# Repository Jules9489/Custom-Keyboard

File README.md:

# Custom-Keyboard

Plan:

65% Keyboard

Rotary Encoder for Media Controls 

Foam Padding in the Case 

Result:

A nice-looking 65% keyboard that has a rotary encoder for media controls.

It took me a while to make because I ran into different problems along the way, but I managed to fix them eventually. I learned a bit of RMK and a bit more about PCB design, as I had previously made a MacroPad using QMK but had a few flaws, and so I was able to learn from my previous mistakes to make this project better. I built this because I was going to buy a keyboard for my laptop, but then I saw this competition and decided to do it myself.

https://cad.onshape.com/documents/b6e58a4c59b5eab8ab909f70/w/83c04b1bc76860f5f25fe353/e/ed9d0ab061e5040caacf7854

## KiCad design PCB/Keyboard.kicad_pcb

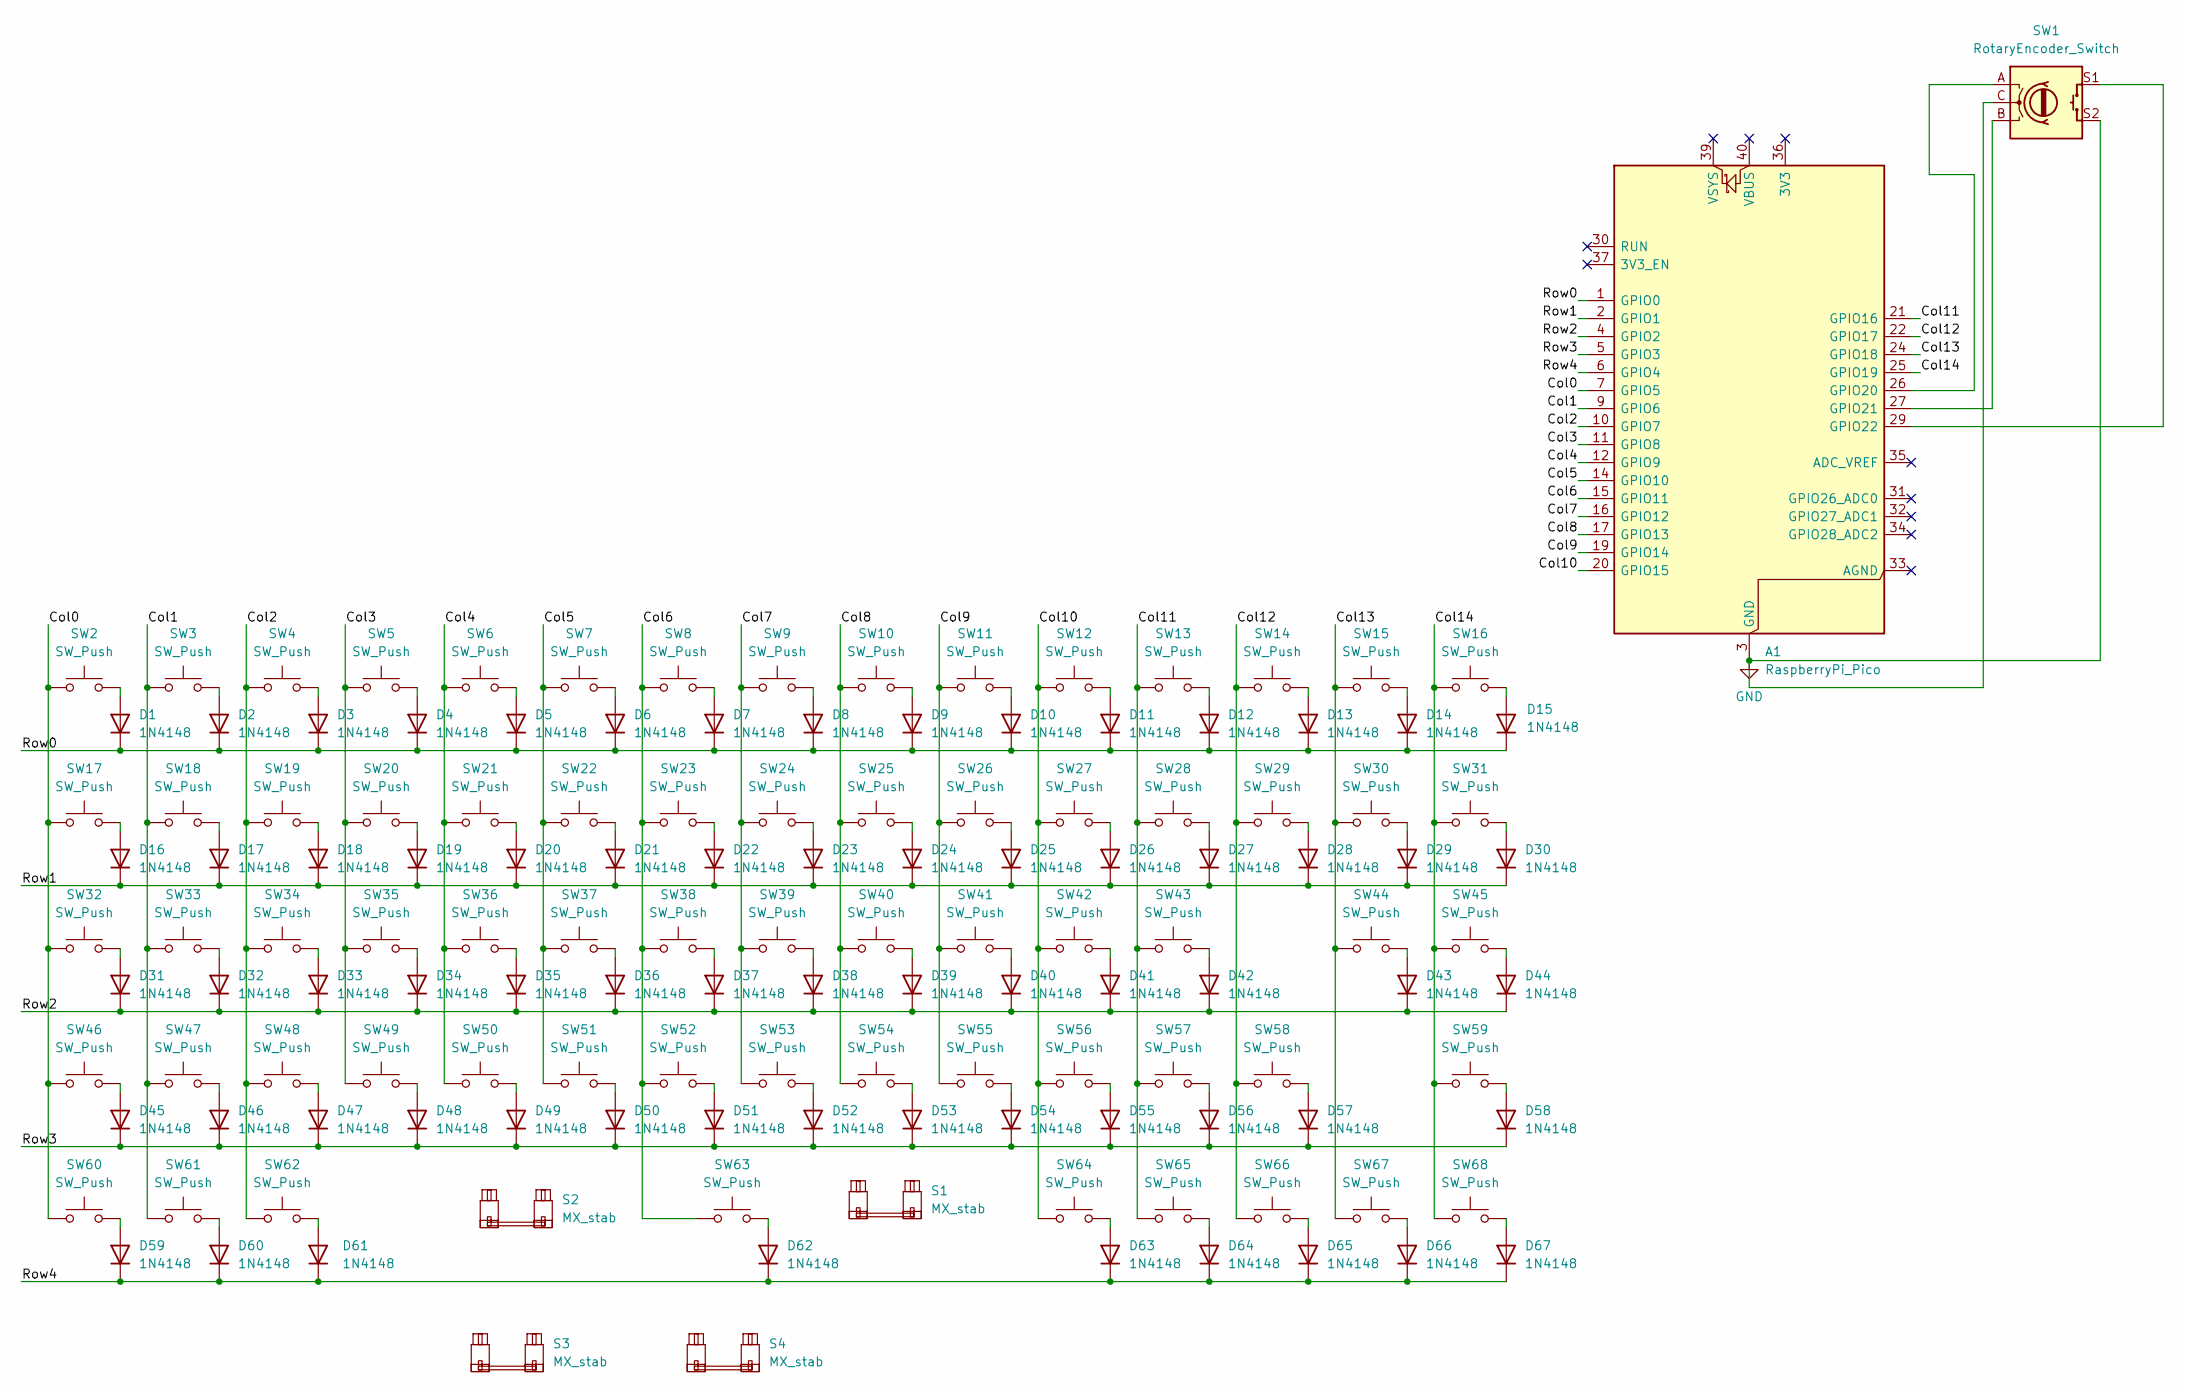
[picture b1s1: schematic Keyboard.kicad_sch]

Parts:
A1: RaspberryPi_Pico; RaspberryPi_Pico_Common_THT
D1, D2, D3, D4, D5, D6, D7, D8, D9, D10, D11, D12, D13, D14, D15, D16, D17, D18, D19, D20, D21, D22, D23, D24, D25, D26, D27, D28, D29, D30, D31, D32, D33, D34, D35, D36, D37, D38, D39, D40, D41, D42, D43, D44, D45, D46, D47, D48, D49, D50, D51, D52, D53, D54, D55, D56, D57, D58, D59, D60, D61, D62, D63, D64, D65, D66, D67: 1N4148; D_DO-35_SOD27_P7.62mm_Horizontal
S1: MX_stab; STAB_MX_P_6.25u
S2: MX_stab; STAB_MX_P_2.25u
S3, S4: MX_stab; STAB_MX_P_2u
SW1: RotaryEncoder_Switch; ROT_Alps_EC11E-Switch
SW2, SW3, SW4, SW5, SW6, SW7, SW8, SW9, SW10, SW11, SW12, SW13, SW14, SW15, SW16, SW17, SW18, SW19, SW20, SW21, SW22, SW23, SW24, SW25, SW26, SW27, SW28, SW29, SW30, SW31, SW32, SW33, SW34, SW35, SW36, SW37, SW38, SW39, SW40, SW41, SW42, SW43, SW44, SW45, SW46, SW47, SW48, SW49, SW50, SW51, SW52, SW53, SW54, SW55, SW56, SW57, SW58, SW59, SW60, SW61, SW62, SW63, SW64, SW65, SW66, SW67, SW68: SW_Push; SW_MX_1u

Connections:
/Col0: A1.7 (GPIO5), SW2.1, SW17.1, SW32.1, SW46.1, SW60.1
/Col1: A1.9 (GPIO6), SW3.1, SW18.1, SW33.1, SW47.1, SW61.1
/Col2: A1.10 (GPIO7), SW4.1, SW19.1, SW34.1, SW48.1, SW62.1
/Col3: A1.11 (GPIO8), SW5.1, SW20.1, SW35.1, SW49.1
/Col4: A1.12 (GPIO9), SW6.1, SW21.1, SW36.1, SW50.1
/Col5: A1.14 (GPIO10), SW7.1, SW22.1, SW37.1, SW51.1
/Col6: A1.15 (GPIO11), SW8.1, SW23.1, SW38.1, SW52.1, SW63.1
/Col7: A1.16 (GPIO12), SW9.1, SW24.1, SW39.1, SW53.1
/Col8: A1.17 (GPIO13), SW10.1, SW25.1, SW40.1, SW54.1
/Col9: A1.19 (GPIO14), SW11.1, SW26.1, SW41.1, SW55.1
/Col10: A1.20 (GPIO15), SW12.1, SW27.1, SW42.1, SW56.1, SW64.1
/Col11: A1.21 (GPIO16), SW13.1, SW28.1, SW43.1, SW57.1, SW65.1
/Col12: A1.22 (GPIO17), SW14.1, SW29.1, SW58.1, SW66.1
/Col13: A1.24 (GPIO18), SW15.1, SW30.1, SW44.1, SW67.1
/Col14: A1.25 (GPIO19), SW16.1, SW31.1, SW45.1, SW59.1, SW68.1
/Row0: A1.1 (GPIO0), D1.1 (K), D2.1 (K), D3.1 (K), D4.1 (K), D5.1 (K), D6.1 (K), D7.1 (K), D8.1 (K), D9.1 (K), D10.1 (K), D11.1 (K), D12.1 (K), D13.1 (K), D14.1 (K), D15.1 (K)
/Row1: A1.2 (GPIO1), D16.1 (K), D17.1 (K), D18.1 (K), D19.1 (K), D20.1 (K), D21.1 (K), D22.1 (K), D23.1 (K), D24.1 (K), D25.1 (K), D26.1 (K), D27.1 (K), D28.1 (K), D29.1 (K), D30.1 (K)
/Row2: A1.4 (GPIO2), D31.1 (K), D32.1 (K), D33.1 (K), D34.1 (K), D35.1 (K), D36.1 (K), D37.1 (K), D38.1 (K), D39.1 (K), D40.1 (K), D41.1 (K), D42.1 (K), D43.1 (K), D44.1 (K)
/Row3: A1.5 (GPIO3), D45.1 (K), D46.1 (K), D47.1 (K), D48.1 (K), D49.1 (K), D50.1 (K), D51.1 (K), D52.1 (K), D53.1 (K), D54.1 (K), D55.1 (K), D56.1 (K), D57.1 (K), D58.1 (K)
/Row4: A1.6 (GPIO4), D59.1 (K), D60.1 (K), D61.1 (K), D62.1 (K), D63.1 (K), D64.1 (K), D65.1 (K), D66.1 (K), D67.1 (K)
GND: A1.3 (GND), A1.8 (GND), A1.13 (GND), A1.18 (GND), A1.23 (GND), A1.28 (GND), A1.38 (GND), SW1.C, SW1.S2
unnamed: A1.26 (GPIO20), SW1.A
unnamed: A1.27 (GPIO21), SW1.B
unnamed: A1.29 (GPIO22), SW1.S1
unnamed: D1.2 (A), SW2.2
unnamed: D2.2 (A), SW3.2
unnamed: D3.2 (A), SW4.2
unnamed: D4.2 (A), SW5.2
unnamed: D5.2 (A), SW6.2
unnamed: D6.2 (A), SW7.2
unnamed: D7.2 (A), SW8.2
unnamed: D8.2 (A), SW9.2
unnamed: D9.2 (A), SW10.2
unnamed: D10.2 (A), SW11.2
unnamed: D11.2 (A), SW12.2
unnamed: D12.2 (A), SW13.2
unnamed: D13.2 (A), SW14.2
unnamed: D14.2 (A), SW15.2
unnamed: D15.2 (A), SW16.2
unnamed: D16.2 (A), SW17.2
unnamed: D17.2 (A), SW18.2
unnamed: D18.2 (A), SW19.2
unnamed: D19.2 (A), SW20.2
unnamed: D20.2 (A), SW21.2
unnamed: D21.2 (A), SW22.2
unnamed: D22.2 (A), SW23.2
unnamed: D23.2 (A), SW24.2
unnamed: D24.2 (A), SW25.2
unnamed: D25.2 (A), SW26.2
unnamed: D26.2 (A), SW27.2
unnamed: D27.2 (A), SW28.2
unnamed: D28.2 (A), SW29.2
unnamed: D29.2 (A), SW30.2
unnamed: D30.2 (A), SW31.2
unnamed: D31.2 (A), SW32.2
unnamed: D32.2 (A), SW33.2
unnamed: D33.2 (A), SW34.2
unnamed: D34.2 (A), SW35.2
unnamed: D35.2 (A), SW36.2
unnamed: D36.2 (A), SW37.2
unnamed: D37.2 (A), SW38.2
unnamed: D38.2 (A), SW39.2
unnamed: D39.2 (A), SW40.2
unnamed: D40.2 (A), SW41.2
unnamed: D41.2 (A), SW42.2
unnamed: D42.2 (A), SW43.2
unnamed: D43.2 (A), SW44.2
unnamed: D44.2 (A), SW45.2
unnamed: D45.2 (A), SW46.2
unnamed: D46.2 (A), SW47.2
unnamed: D47.2 (A), SW48.2
unnamed: D48.2 (A), SW49.2
unnamed: D49.2 (A), SW50.2
unnamed: D50.2 (A), SW51.2
unnamed: D51.2 (A), SW52.2
unnamed: D52.2 (A), SW53.2
unnamed: D53.2 (A), SW54.2
unnamed: D54.2 (A), SW55.2
unnamed: D55.2 (A), SW56.2
unnamed: D56.2 (A), SW57.2
unnamed: D57.2 (A), SW58.2
unnamed: D58.2 (A), SW59.2
unnamed: D59.2 (A), SW60.2
unnamed: D60.2 (A), SW61.2
unnamed: D61.2 (A), SW62.2
unnamed: D62.2 (A), SW63.2
unnamed: D63.2 (A), SW64.2
unnamed: D64.2 (A), SW65.2
unnamed: D65.2 (A), SW66.2
unnamed: D66.2 (A), SW67.2
unnamed: D67.2 (A), SW68.2

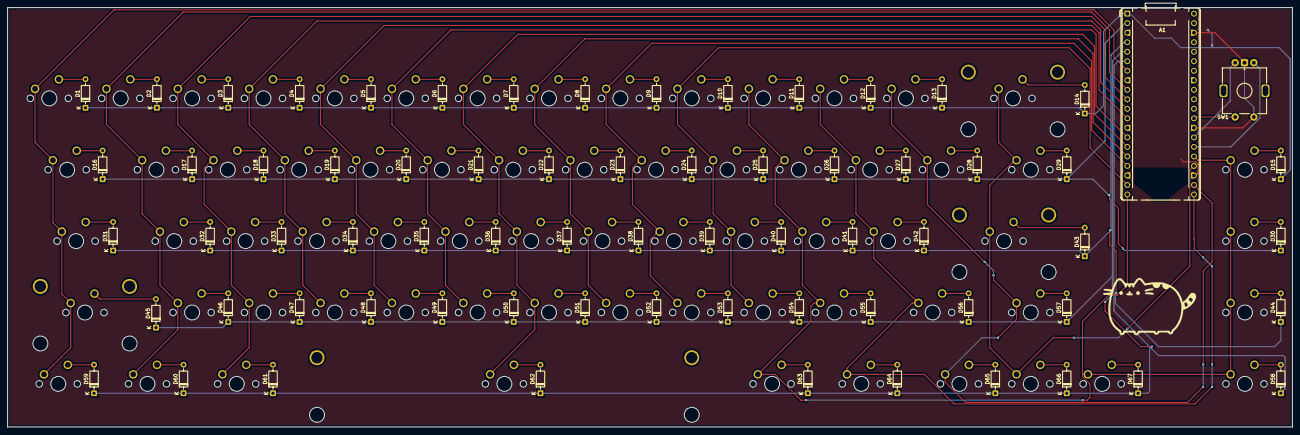
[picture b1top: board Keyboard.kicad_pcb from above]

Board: 2 copper layers, 342.9 x 111.9 mm, 140 parts (0 on the bottom side), 91 nets.

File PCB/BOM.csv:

"Id";"Designator";"Footprint";"Quantity";"Designation";"Supplier and ref";
1;"D39,D10,D55,D16,D58,D1,D57,D61,D18,D30,D64,D28,D23,D45,D41,D66,D2,D62,D56,D4,D29,D38,D24,D22,D43,D17,D21,D12,D52,D53,D25,D9,D5,D31,D42,D11,D37,D6,D60,D49,D36,D63,D51,D67,D20,D8,D32,D65,D15,D19,D48,D47,D7,D3,D54,D14,D46,D26,D13,D44,D33,D40,D59,D35,D27,D50,D34";"D_DO-35_SOD27_P7.62mm_Horizontal";67;"1N4148";;;
2;"SW52,SW11,SW24,SW63,SW28,SW12,SW38,SW57,SW55,SW8,SW16,SW17,SW26,SW61,SW58,SW40,SW51,SW50,SW4,SW15,SW56,SW2,SW47,SW41,SW44,SW39,SW67,SW10,SW21,SW9,SW45,SW59,SW49,SW19,SW43,SW14,SW3,SW53,SW20,SW13,SW54,SW30,SW36,SW27,SW34,SW48,SW31,SW33,SW65,SW7,SW66,SW64,SW46,SW42,SW5,SW32,SW25,SW23,SW18,SW22,SW68,SW62,SW6,SW35,SW60,SW37,SW29";"SW_MX_1u";67;"SW_Push";;;
3;"S3,S4";"STAB_MX_P_2u";2;"MX_stab";;;
4;"S2";"STAB_MX_P_2.25u";1;"MX_stab";;;
5;"S1";"STAB_MX_P_6.25u";1;"MX_stab";;;
6;"SW1";"ROT_Alps_EC11E-Switch";1;"RotaryEncoder_Switch";;;
7;"A1";"RaspberryPi_Pico_Common_THT";1;"RaspberryPi_Pico";;;
